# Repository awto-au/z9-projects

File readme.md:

- Note re projhect UUIDs

- IMPORTANT: avoid duplicate schematic UUIDs across shared files

If a shared sheet is copied/renamed (for example in `z9-shared/`), make sure the copied `.kicad_sch` does not keep the same top-level `(uuid "...")` as another active sheet file.

Duplicate UUIDs can cause confusing behavior: sheets may fail to load correctly, references can point to the wrong sheet content, and project/sheet-instance mapping can become unstable.

Safe practice when duplicating a sheet:

- duplicate the file
- open it in KiCad and save-as / resave so a new UUID is generated, or manually replace the top-level UUID with a new one
- re-open the parent project and verify the `Sheetfile` path and `sheet_instances` resolve to the intended file

## Shared Sheet Architecture (as of 2026-04-29)

This repository uses a mixed architecture where core modules are shared across multiple projects via `z9-shared/`, while project-specific functionality remains local.

### Truly Shared Sheets (common UUID across projects)

These sheets have the same top-level UUID and represent unified modules used by multiple projects:

| Sheet Name | UUID | Projects Using | Purpose |
|---|---|---|---|
| shared_usbc.kicad_sch | `1f11bca8-5815-40a7-b8ee-263189e52167` | PDM, console, core | USB Type-C connectivity & power |
| shared_isolated_can.kicad_sch | `01fd732b-d28d-4591-958a-cdee10605b4f` | PDM, console, core | Isolated CAN bus interface |
| shared_ism330dhcx.kicad_sch | `c1bd34f9-1a2e-4e3d-a058-d6dd5157e270` | PDM, console, core | 6-axis IMU / accelerometer |
| shared_buzzer.kicad_sch | `58de86fb-6cef-462e-b9e3-6fa5d0bb0e90` | PDM, console, core | Audio/feedback buzzer |

### Project-Specific or Diverged Sheets

These sheets exist with different UUIDs/content across projects:

| Sheet Name | PDM UUID | Console UUID | Status |
|---|---|---|---|
| stm32.kicad_sch | `6cdc1f96-2079-4699-9b8b-64cd08d3349d` (33K lines) | `4182fd16-8ac6-4c4f-8a6b-17b87a3a1318` (26K lines) | ✅ DE-DUPLICATED — assigned unique UUIDs after significant content divergence |
| connectors.kicad_sch | `62522fec-fb26-4067-a233-5bb78faa120b` | `ff807900-38a7-468c-8c88-36815649564b` | Different modules, project-specific |
| untitled.kicad_sch (power) | `4ea6699b-0436-432c-816e-7adf1044fb41` | `f4d1610f-a9d7-400f-8201-07e24024a234` | Different modules, project-specific |

#### stm32 Divergence Details (resolved 2026-04-29)

PDM and console both previously referenced stm32.kicad_sch with the same UUID (`b85e7fcc-fcb8-4f3f-b9d9-a567574ce4fb`), but the files had diverged significantly:

**PDM stm32 (33K lines, older 2022-04-10 metadata):**
- Comprehensive embedded symbol library (JLCPCB capacitors, resistors)
- ST connector types (STDC14, TagConnect)
- Crystal oscillators (8MHz)
- Specialized connectors (DF40HC3.0-100DS-0.4V51)
- More detailed layout/definitions
- Metadata: "title l8", "company DNT"

**Console stm32 (26K lines, newer 2026 metadata):**
- Simplified schematic focused on MCU core
- Test points instead of dedicated connectors
- Metadata: "company Zero9 - 0-9.au", "Some schematic is shared"

**Resolution:**
- PDM stm32 now UUID: `6cdc1f96-2079-4699-9b8b-64cd08d3349d`
- Console stm32 now UUID: `4182fd16-8ac6-4c4f-8a6b-17b87a3a1318`

These are now independent modules that should not be assumed to be interchangeable. Future maintainers should treat them as separate designs and explicitly sync if unification is desired.

### Console-Only Sheets

- shared_usbc_esp32.kicad_sch (`7f987ba3-810e-4341-b9d4-ad527c98f4c1`) — ESP32 variant of USB-C module

### Core Design Structure (rebuilt 2026-04-29)

Core is now a hierarchical module that references only the truly shared sheets in `z9-shared/`:

```
z9-core.kicad_sch (root)
  ├── z9-shared/shared_usbc.kicad_sch
  ├── z9-shared/shared_isolated_can.kicad_sch
  ├── z9-shared/shared_ism330dhcx.kicad_sch
  └── z9-shared/shared_buzzer.kicad_sch
```

### UUID Deduplication (completed 2026-04-29)

Several shared files had duplicate UUIDs that have since been fixed:

| File | Old UUID | New UUID | Reason |
|---|---|---|---|
| usbc.kicad_sch | `1f11bca8-5815-40a7-b8ee-263189e52167` | `fa8ae3e9-6b30-442f-8590-d93320e7db7b` | Copy of shared_usbc; renamed to prevent collision |
| shared.kicad_sch | `1f11bca8-5815-40a7-b8ee-263189e52167` | `6e9f9a04-b3f3-4667-a147-eb1a8952cf4f` | Duplicate of shared_usbc; fixed |
| shared_5V_LMR54410.kicad_sch | `a7202c14-0f41-48d8-b26c-392947ef0c55` | `c6e889f8-d252-47bb-acac-ee7397c7ab1d` | Duplicate of shared_5V_LMR14206; fixed |

stored in [project name].kicad_pro

snup ####################
  "sheets": [
    [
      "8d063f79-9282-4820-bcf4-1ff3c006cf08",
      "Root"
    ],

then 'root' schmeatic 
snip ############
(kicad_sch
	(version 20250114)
	(generator "eeschema")
	(generator_version "9.0")
	(uuid "8d063f79-9282-4820-bcf4-1ff3c006cf08")
	(paper "A3")
	(title_block
		(date "2024-05-30")
	)

-- project uuids
old pdm 8d063f79-9282-4820-bcf4-1ff3c006cf08
new pdm b643db5c-578e-4b48-aafc-cc4190db582a

shared 

new 0d832c56-2071-4d02-b574-dc412c8c5a75

8d063f79-9282-4820-bcf4-1ff3c006cf08

- KiCad library setup notes

KiCad path management is not the only setting required for these projects.
For the PDM project, the symbol and footprint library tables also need to be configured so ERC can resolve the custom libraries used by the design.

Required custom libraries:

- `dnt_global` = my global symbols
- `dnt` = my global footprints

What was found:

- Project-local footprint table: [z9-pdm/fp-lib-table](/home/dan/git/z9-projects/z9-pdm/fp-lib-table)
- Project-local symbol table: [z9-pdm/sym-lib-table](/home/dan/git/z9-projects/z9-pdm/sym-lib-table)
- Global KiCad footprint table: `/home/dan/.config/kicad/10.0/fp-lib-table`
- Global KiCad symbol table: `/home/dan/.config/kicad/10.0/sym-lib-table`
- The PDM project tables were effectively empty, so KiCad was falling back to global configuration.
- `dnt_global` was configured globally on this machine at `/home/dan/git/dnt.kicad.libs/symbols/dnt_global.kicad_sym`
- `dnt` was configured globally on this machine at `/home/dan/git/dnt.kicad.libs/footprints/dnt.pretty`
- KiCad 10 third-party alternate library content was found under `/home/dan/.local/share/kicad/10.0/3rdparty/`
- That third-party content includes AKL resistor/capacitor/diode libraries, but not exact `PCM_JLCPCB*` library names in the global tables.

Current project-local fix added for PDM:

- `z9-pdm/sym-lib-table` now maps `dnt_global`
- `z9-pdm/sym-lib-table` now maps `PCM_Espressif` to `dnt_global.kicad_sym` because the required ESP32-S3 symbol was already embedded there
- `z9-pdm/fp-lib-table` now maps `dnt`
- `z9-pdm/fp-lib-table` now maps `PCM_Espressif` to `dnt.kicad.libs/footprints/PCM_Espressif.pretty`
- `z9-pdm/sym-lib-table` also maps `PCM_JLCPCB-Resistors`, `PCM_JLCPCB-Capacitors`, and `PCM_JLCPCB-Diodes` to get ERC closer to usable
- `z9-pdm/fp-lib-table` also maps `PCM_JLCPCB`
- The required Espressif footprint files `ESP32-S3-WROOM-1.kicad_mod` and `ESP32-S3-WROOM-1U.kicad_mod` were copied from `https://github.com/espressif/kicad-libraries` into `dnt.kicad.libs/footprints/PCM_Espressif.pretty`
- The matching Espressif STEP models were copied into `dnt.kicad.libs/models/`

Result:

- ERC on PDM dropped from `1 error, 675 warnings` to `1 error, 229 warnings`
- Most of the missing-library noise was removed
- `PCM_Espressif` now resolves from repo-local library content instead of requiring a separate KiCad add-on install on this machine
- Remaining warnings show that some `PCM_JLCPCB*` symbols and footprints still do not exist under the currently available local libraries, so installing or restoring the original PCM/JLC libraries is still needed for a clean ERC result

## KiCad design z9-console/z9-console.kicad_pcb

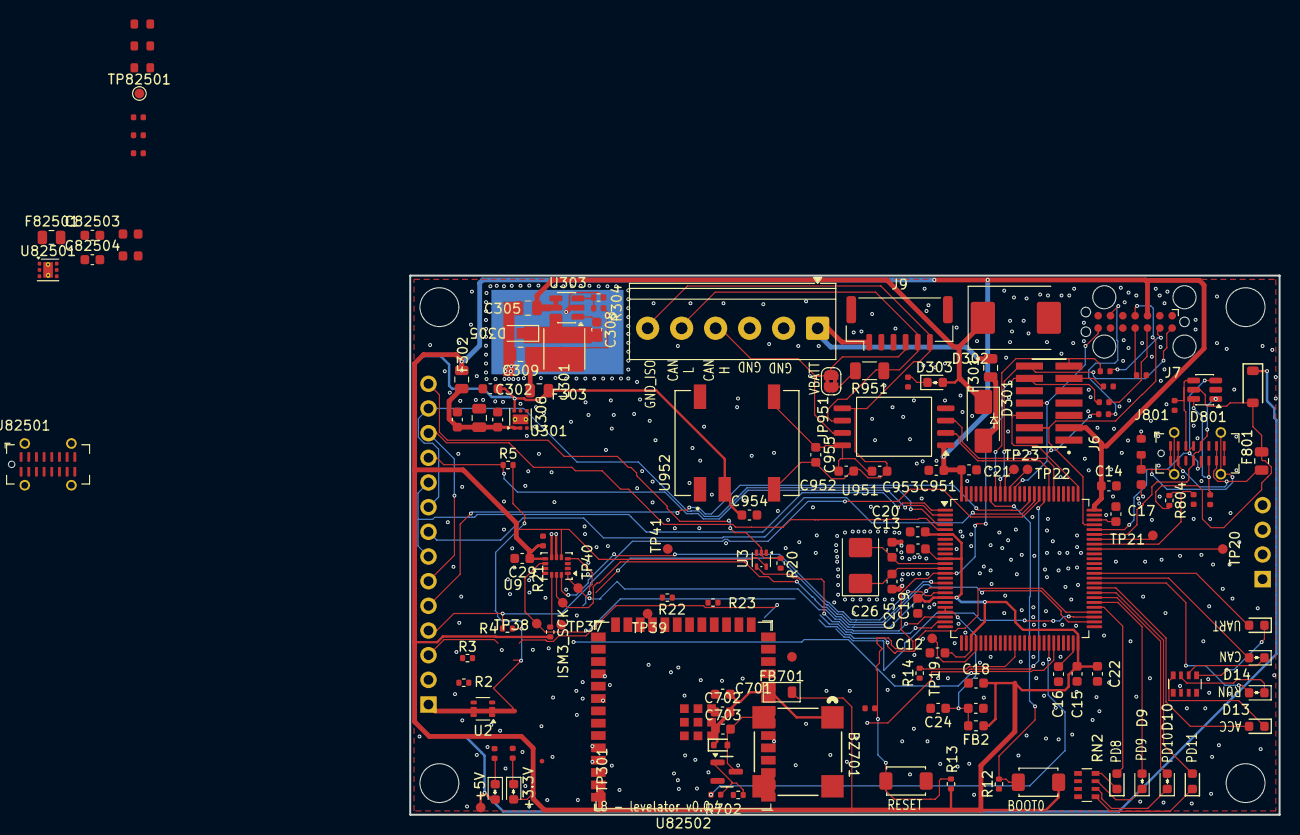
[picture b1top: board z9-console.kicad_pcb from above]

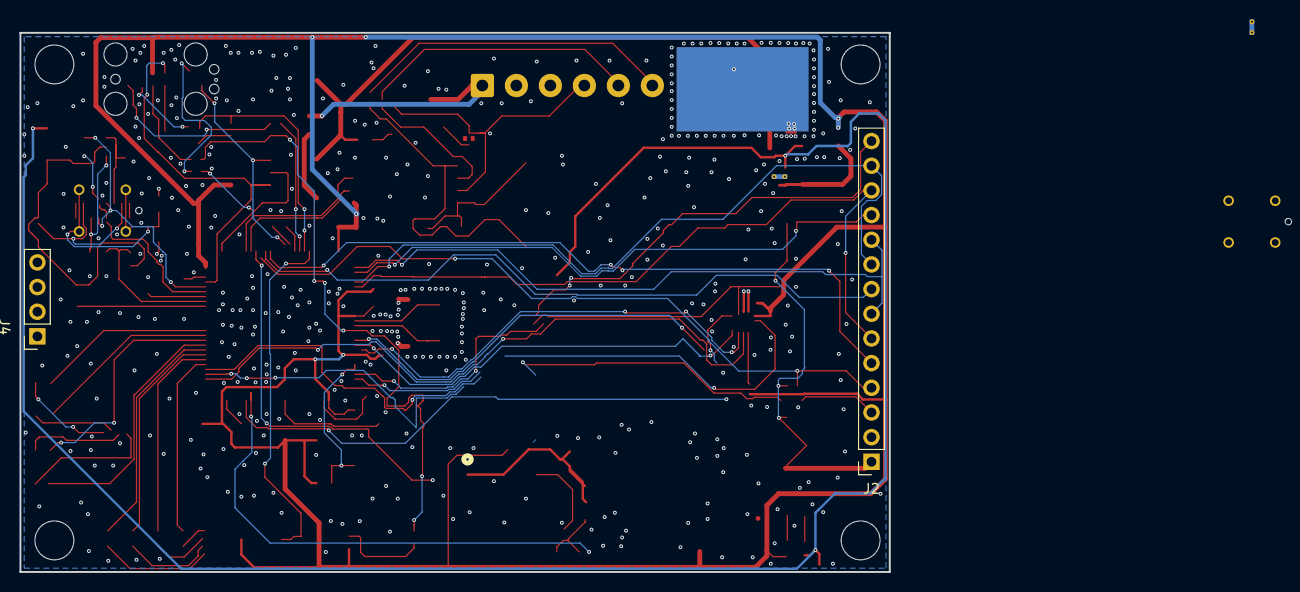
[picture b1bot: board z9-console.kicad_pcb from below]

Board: 2 copper layers, 89.5 x 55.5 mm, 143 parts (2 on the bottom side), 100 nets.

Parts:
BZ701: Buzzer_-_MLT-8530; Buzzer - MLT-8530_JHE
C11: 10nF; C_0402
C12, C13, C14, C15, C18, C19, C20, C21, C24, C306, C308, C702, C703, C951, C953, C82503: 100nF; C_0603_1608Metric
C16, C17: 2.2uF; C_0603_1608Metric
C22, C29, C302, C701, C952, C954, C955, C82504: 10uF; C_0603_1608Metric
C23, C303: 1uF; C_0603_1608Metric
C25, C26: 18pF; C_0603_1608Metric
C28: 100nF; C_0402
C304, C309: 22uF; C_0805_2012Metric
C305: 10uF; C_0805_2012Metric
C801: 47nF; C_0603
C82501, C82502: 10uF; C_0603
D8, D11, D12, D15: LED-YELLOW; D_0603
D9, D13: LED-WHITE; LED_0603_1608Metric - polarity
D10, D14, D303, D304, D306: LED-RED; LED_0603_1608Metric - polarity
D301: SS54; D_SMA - polarity
D302: SM15T100CA; D_SMC
D305: V1P6-M3/H 60V 1A; D_MicroSMP_AK
D701: RB751S-40; D_SOD-523
D801: SRV05-4; SOT-23-6
D802: B5819W SL; D_SOD-123
F301, F302, F303, F801: Fuse; Fuse_0805_2012Metric
F82501: Fuse_16V_500mA_100A_1A_150mΩ_0805_PTC; Fuse_0805_2012Metric
FB2: 4.7uH; L_0603_1608Metric
FB701: F_0805_2012Metric
H901, H902, H903, H904: MountingHole; MountingHole_4mm
J2: LCD 3.2" 240x320 Conn_01x14_Pin; PinSocket_1x14_P2.54mm_Vertical
J4: Conn_01x04_Pin; PinSocket_1x04_P2.54mm_Vertical
J6: ST_STDC14 - SAMTEC_FTSH-107-01-F-DV-K-Fix; Conn_SAMTEC_FTSH-107-01-F-DV-K-Fix
J7: TC2070 - TAG Connect; Tag-Connect_TC2070-IDC-FP_2x07_P1.27mm_Vertical
J9: JST GH; JST_GH_BM06B-GHS-TBT_1x06-1MP_P1.25mm_Vertical
J10: Screw_Terminal_01x06; TerminalBlock_Phoenix_PT-1,5-6-3.5-H_1x06_P3.50mm_Horizontal
J801, J82501: USB_C_Receptacle_USB2.0_16P; USB_C_Receptacle_G-Switch_GT-USB-7051x
JP951: SolderJumper_2_Bridged; SolderJumper-2_P1.3mm_Bridged2Bar_RoundedPad1.0x1.5mm
L301: 3.3uH; L_Sunlord_SWPA4030S
Q701: AO3400A; Q_SOT-23
R2, R3, R4, R5, R12, R13, R14, R20, R21, R22, R23, R304, R702, R804: 10K; R_0402_1005Metric
R15, R16, R17, R18, R19, R701: 100R; R_0402
R301, R302, R305: 2.2K; R_0402
R303: 56K; R_0402
R801: 1MΩ; R_0603
R802, R803, R82504, R82505, R82506: 5.1kΩ; R_0402
R805: 2.2k; R_0402
R951: 120R; R_1206_3216Metric
R82501, R82502: 100kΩ; R_0603
R82503: 47Ω; R_0603
RN2, RN3: 1k; R_Array_Convex_4x0603
SW2, SW3: SW_Push; SW_TS-1088-AR02016
TP18: PA1; TestPoint_Pad_D1.0mm FP .6R
TP19: PA4; TestPoint_Pad_D1.0mm FP .6R
TP20: PA8; TestPoint_Pad_D1.0mm FP .6R
TP21: PA10; TestPoint_Pad_D1.0mm FP .6R
TP22: PB4; TestPoint_Pad_D1.0mm FP .6R
TP23: PB5; TestPoint_Pad_D1.0mm FP .6R
TP37: ISM_CS; TestPoint_Pad_D1.0mm FP .6R
TP38: ISM_INT1; TestPoint_Pad_D1.0mm FP .6R
TP39: ISM_INT2; TestPoint_Pad_D1.0mm FP .6R
TP40: ISM_SDO; TestPoint_Pad_D1.0mm FP .6R
TP41: ISM_SDI; TestPoint_Pad_D1.0mm FP .6R
TP42: ISM3_SCK; TestPoint_Pad_D1.0mm FP .6R
TP301: +3.3V; TestPoint_Pad_D1.0mm FP .6R
TP302: 5V; TestPoint_Pad_D1.0mm FP .6R
TP82501: PE0; TestPoint_Pad_D1.0mm
U2: TPS22919DCKR; SOT-363_SC-70-6
U3: SN74LVC1G14DRLR; SOT-553
U8: STM32F427V_G-I_Tx; LQFP-100_14x14mm_P0.5mm
U9: ISM330DHCX; LGA-14_3x2.5mm_P0.5mm_LayoutBorder3x4y
U301, U82501: TLV76733DRVx; WSON-6-1EP_2x2mm_P0.65mm_EP1x1.6mm_ThermalVias
U303: LMR14006YDDCR; SOT-23-6
U951: ISO1042-Q1; SOIC-8_7.5x5.85mm_P1.27mm
U952: B0505XT-1WR3; B0505_Isolated_SMD
U82502: ESP32-S3-WROOM-1; ESP32-S3-WROOM-1U
X2: 8MHz 20pF; Crystal_SMD_5032-2Pin_5.0x3.2mm

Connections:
+3.3V: C12.2, C13.2, C14.2, C15.2, C18.2, C19.2, C20.2, C21.2, C22.2, C28.1, C29.1, C951.1, D304.2 (A), F302.2, FB2.1, FB701.2, J6.3 (VCC), J7.3 (VCC), R13.1, R21.2, SW2.2 (B), TP301.1, U2.1 (VIN), U3.5 (VCC), U8.6 (VBAT), U8.11 (VDD), U8.19 (VDD), U8.28 (VDD), U8.50 (VDD), U8.75 (VDD), U8.100 (VDD), U9.5 (VDDIO), U9.8 (VDD), U951.1 (VCC1)
+5V: C302.1, C954.1, C82501.1, D306.2 (A), D802.1, F303.2, TP302.1, U301.6 (IN), U952.2 (+VIN), U82501.6 (IN)
/+5V_ISO: C952.1, C953.1, C955.1, U951.8 (VCC2), U952.5 (+VOUT)
/CAN1_RX: U8.81 (PD0), U951.3 (RXD)
/CAN1_TX: U8.82 (PD1), U951.2 (TXD)
/CAN_H: J9.4, J10.4, JP951.2 (B), U951.7 (CANH)
/CAN_L: J9.5, J10.5, R951.1, U951.6 (CANL)
/GND_ISO: C952.2, C953.2, C955.2, J9.6, J10.6, U951.5 (GND2), U952.4 (-VOUT)
/LCD_DC: J2.5 (D/C), U8.86 (PD5)
/LCD_LED: J2.8 (LED), U8.85 (PD4)
/LCD_ON: R2.2, U2.3 (ON), U8.45 (PE14)
/LCD_RESET: J2.4 (RESET), R4.1, U8.84 (PD3)
/MCU/BOOT0: R12.2, SW2.1 (A), U8.94 (BOOT0)
/MCU/BOOT1: R14.2, U8.37 (PB2)
/MCU/NRST: C11.2, J6.12 (~RST), R13.2, R17.1, SW3.2 (B), U8.14 (NRST)
/MCU/PA1: TP18.1, U8.24 (PA1)
/MCU/PA4: TP19.1, U8.29 (PA4)
/MCU/PA8: TP20.1, U8.67 (PA8)
/MCU/PB4: TP22.1, U8.90 (PB4)
/MCU/PB5: TP23.1, U8.91 (PB5)
/MCU/PD8: D8.2, U8.55 (PD8)
/MCU/PD9: D9.2 (A), U8.56 (PD9)
/MCU/PD10: D10.2 (A), U8.57 (PD10)
/MCU/PD11: D11.2, U8.58 (PD11)
/MCU/PD12: D12.2, U8.59 (PD12)
/MCU/PD13: D13.2 (A), U8.60 (PD13)
/MCU/PD14: D14.2 (A), U8.61 (PD14)
/MCU/PD15: D15.2, U8.62 (PD15)
/MCU/RCC_OSC_IN: C25.1, U8.12 (PH0), X2.2
/MCU/RCC_OSC_OUT: C26.1, U8.13 (PH1), X2.1
/MCU/SYS_JTCK-SWCLK: J6.6 (JCLK/SWCLK), R18.1, U8.76 (PA14)
/MCU/SYS_JTDO-SWO: J6.8 (JTDO/SWO), J7.8 (JTDO/SWO), U8.89 (PB3)
/MCU/SYS_JTMS-SWDIO: J6.4 (JTMS/SWDIO), J7.4 (JTMS/SWDIO), U8.72 (PA13)
/MCU/USART1_RX: J6.13 (VCP_RX), R19.1, U8.93 (PB7)
/MCU/USART1_TX: J6.14 (VCP_TX), J7.14 (VCP_TX), U8.92 (PB6)
/PE13: R701.2, U8.44 (TIM1_CH3)
/SPI2_CS: R21.1, TP37.1, U8.16 (PC1), U9.12 (CS)
/SPI2_IRQ: R22.2, TP39.1, U8.53 (PB14), U9.4 (INT1)
/SPI2_IRQ2: R23.2, TP38.1, U8.54 (PB15), U9.9 (INT2)
/SPI2_SCK: TP42.1, U8.52 (PB13), U9.13 (SCL)
/SPI2_SDI: TP40.1, U8.17 (PC2), U9.1 (SDO/SA0)
/SPI2_SDO: TP41.1, U8.18 (PC3), U9.14 (SDA)
/SPI4_CS_1: J2.11 (T_CS), R5.1, U8.2 (PE3)
/SPI4_CS_2: J2.3 (CS), R3.1, U8.83 (PD2)
/SPI4_SCK: J2.7 (SCK), J2.10 (T_SCK), U8.1 (PE2)
/SPI4_SDI: J2.9 (SDO), J2.13 (T_SDO), U8.4 (PE5)
/SPI4_SDO: J2.6 (SDI), J2.12 (T_SDI), U8.5 (PE6)
/SYS_WAKEUP: U3.4, U8.23 (PA0)
/USB_OTG_FS_DM: D801.1, J801.A7 (D-), J801.B7 (D-), U8.70 (PA11)
/USB_OTG_FS_DP: D801.3, J801.A6 (D+), J801.B6 (D+), U8.71 (PA12)
/USB_OTG_FS_VBUS: R804.1, R805.2, U8.68 (PA9)
/VBATT: F301.1, J9.1, J10.1
/shared_esp32/ESP_EN: R82501.1, U82502.3 (EN)
GND: C11.1, C12.1, C13.1, C14.1, C15.1, C16.2, C17.2, C18.1, C19.1, C20.1, C21.1, C22.1, C23.1, C24.2, C25.2, C26.2, C28.2, C29.2, C302.2, C303.1, C304.2, C305.2, C306.2, C309.2, C701.2, C702.1, C801.2, C951.2, C954.2, C82501.2, C82502.2, C82503.2, C82504.2, D302.2 (A2), D305.2 (A), D801.2, J2.2 (GND), J6.5 (GND), J6.7 (GND), J7.5 (GND), J7.7 (GND), J9.2, J9.3, J10.2, J10.3, J801.A1 (GND), J801.A12 (GND), J801.B1 (GND), J801.B12 (GND), J82501.A1 (GND), J82501.A12 (GND), J82501.B1 (GND), J82501.B12 (GND), J82501.S1 (SHIELD), Q701.2 (S), R2.1, R12.1, R14.1, R15.2, R16.2, R20.1, R22.1, R23.1, R301.1, R302.1, R304.1, R305.1, R702.1, R801.2, R802.1, R803.1, R805.1, R82501.2, R82505.1, R82506.1, RN2.5 (R4.2), RN2.6 (R3.2), RN2.7 (R2.2), RN2.8 (R1.2), RN3.5 (R4.2), RN3.6 (R3.2), RN3.7 (R2.2), RN3.8 (R1.2), SW3.1 (A), U2.2 (GND), U3.3 (GND), U8.10 (VSS), U8.20 (VSSA), U8.27 (VSS), U8.74 (VSS), U8.99 (VSS), U9.6 (GND), U9.7 (GND), U301.3 (GND), U301.5 (GND), U301.7 (PAD), U303.2 (GND), U951.4 (GND1), U952.1 (-VIN), U82501.3 (GND), U82501.5 (GND), U82501.7 (PAD), U82502.1 (GND), U82502.40 (GND), U82502.41 (GND)
unnamed: BZ701.1 (+), C701.1, C702.2, C703.1, D701.1, FB701.1
unnamed: BZ701.2 (-), C703.2, D701.2, Q701.3 (D)
unnamed: C309.1, F303.1, L301.2, R303.1
unnamed: D9.1 (K), RN2.3 (R3.1)
unnamed: D10.1 (K), RN2.2 (R2.1)
unnamed: D13.1 (K), RN3.3 (R3.1)
unnamed: D14.1 (K), RN3.2 (R2.1)
unnamed: D301.2 (A), F301.2
unnamed: C305.1, D301.1 (K), D302.1 (A1), D303.2 (A), U303.4 (~SHDN), U303.5 (VIN)
unnamed: D303.1 (K), R301.2
unnamed: D304.1 (K), R302.2
unnamed: C308.2, D305.1 (K), L301.1, U303.6 (SW)
unnamed: D306.1 (K), R305.2
unnamed: D801.5, D802.2, F801.2, R804.2
unnamed: F801.1, J801.A4 (VBUS), J801.A9 (VBUS), J801.B4 (VBUS), J801.B9 (VBUS)
unnamed: J2.14 (T_IRQ), R20.2, U3.2
unnamed: J2.1 (VCC), R3.2, R4.2, R5.2, U2.5 (QOD), U2.6 (VOUT)
unnamed: J6.11 (GNDDetect), R15.1
unnamed: J7.11 (GNDDetect), R16.1
unnamed: J7.6 (JCLK/SWCLK), R18.2
unnamed: J7.13 (VCP_RX), R19.2
unnamed: J7.12 (~RST), R17.2
unnamed: D801.4, J801.A5 (CC1), R803.2
unnamed: D801.6, J801.B5 (CC2), R802.2
unnamed: C801.1, J801.S1 (SHIELD), R801.1
unnamed: J82501.A5 (CC1), R82506.2
unnamed: J82501.B5 (CC2), R82505.2
unnamed: JP951.1 (A), R951.2
unnamed: Q701.1 (G), R701.1, R702.2
unnamed: D11.1, RN2.1 (R1.1)
unnamed: D8.1, RN2.4 (R4.1)
unnamed: D15.1, RN3.1 (R1.1)
unnamed: D12.1, RN3.4 (R4.1)
unnamed: TP21.1, U8.69 (PA10)
unnamed: C16.1, U8.49 (VCAP_1)
unnamed: C17.1, U8.73 (VCAP_2)
unnamed: C23.2, C24.1, FB2.2, U8.21 (VREF+), U8.22 (VDDA)
unnamed: C303.2, C304.1, C306.1, F302.1, U301.1 (OUT), U301.2 (SNS)
unnamed: C308.1, U303.1 (CB)
unnamed: R303.2, R304.2, U303.3 (FB)
unnamed: C82502.1, F82501.1, U82501.1 (OUT), U82501.2 (SNS)
unnamed: C82503.1, C82504.1, F82501.2, R82502.1, TP82501.1, U82502.2 (3V3)
unnamed: R82502.2, R82504.1, U82502.27 (GPIO0/BOOT)
unnamed: J82501.A7 (D-), J82501.B7 (D-), U82502.13 (GPIO19/U1RTS/ADC2_CH8/CLK_OUT2/USB_D-)
unnamed: J82501.A6 (D+), J82501.B6 (D+), U82502.14 (GPIO20/U1CTS/ADC2_CH9/CLK_OUT1/USB_D+)
unnamed: R82503.1, U82502.37 (U0TXD/GPIO43/CLK_OUT1)

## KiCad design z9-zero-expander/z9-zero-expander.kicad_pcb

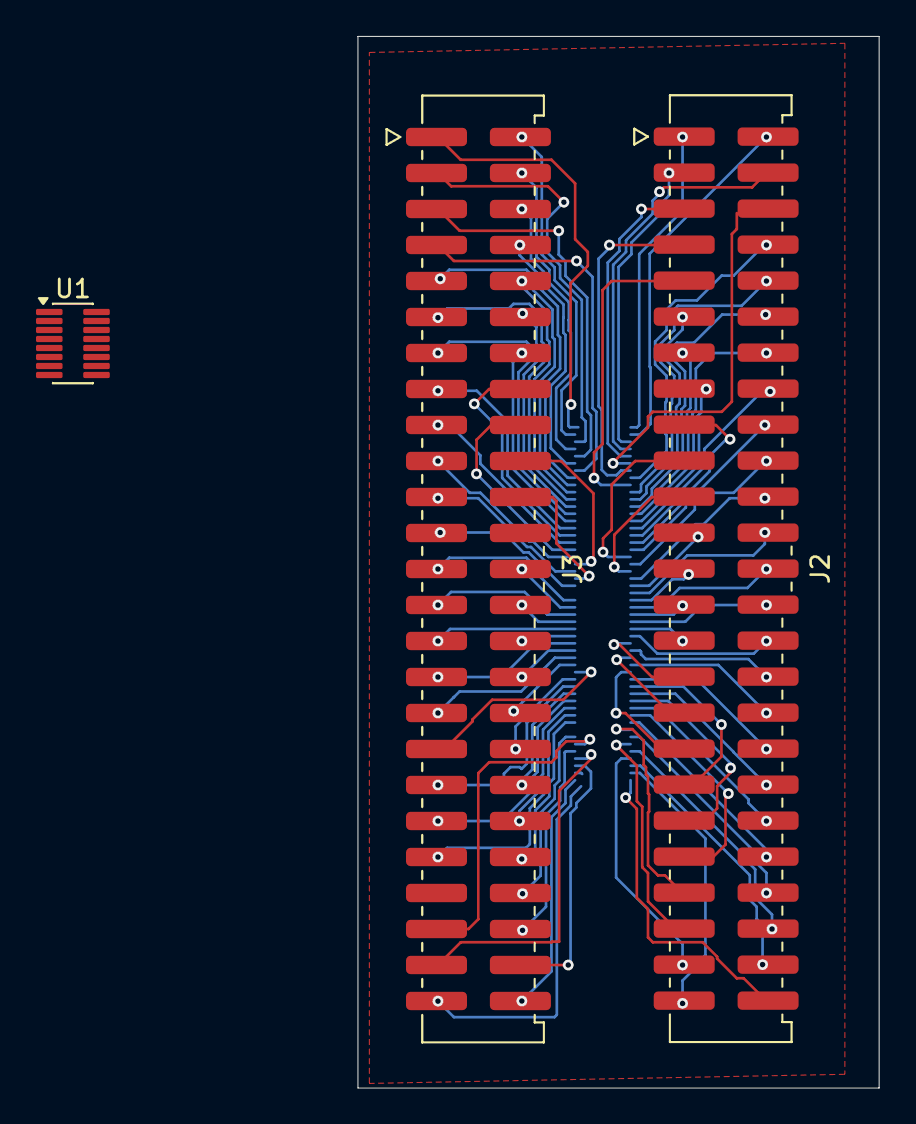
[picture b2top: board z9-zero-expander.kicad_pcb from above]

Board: 2 copper layers, 29.0 x 58.4 mm, 4 parts (1 on the bottom side), 100 nets.

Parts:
J1: Conn_DF40HC3.0-100DP-0.4V51; Hirose_DF40C-100DP-0.4V_2x50-1MP_P0.4mm
J2, J3: Conn_01x50; Samtec_LTMM-125-02-X-D-SM_2x25_P2.0mm_Header_Vertical
U1: TMUX1574DYY; Texas_DYY0016A_TSOT-23-16_2x4.2mm_P0.5mm

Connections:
unnamed: J1.51, J2.1
unnamed: J1.52, J2.2
unnamed: J1.53, J2.3
unnamed: J1.54, J2.4
unnamed: J1.55, J2.5
unnamed: J1.56, J2.6
unnamed: J1.57, J2.7
unnamed: J1.58, J2.8
unnamed: J1.59, J2.9
unnamed: J1.60, J2.10
unnamed: J1.61, J2.11
unnamed: J1.62, J2.12
unnamed: J1.63, J2.13
unnamed: J1.64, J2.14
unnamed: J1.65, J2.15
unnamed: J1.66, J2.16
unnamed: J1.67, J2.17
unnamed: J1.68, J2.18
unnamed: J1.69, J2.19
unnamed: J1.70, J2.20
unnamed: J1.71, J2.21
unnamed: J1.72, J2.22
unnamed: J1.73, J2.23
unnamed: J1.74, J2.24
unnamed: J1.75, J2.25
unnamed: J1.76, J2.26
unnamed: J1.77, J2.27
unnamed: J1.78, J2.28
unnamed: J1.79, J2.29
unnamed: J1.80, J2.30
unnamed: J1.81, J2.31
unnamed: J1.82, J2.32
unnamed: J1.83, J2.33
unnamed: J1.84, J2.34
unnamed: J1.85, J2.35
unnamed: J1.86, J2.36
unnamed: J1.87, J2.37
unnamed: J1.88, J2.38
unnamed: J1.89, J2.39
unnamed: J1.90, J2.40
unnamed: J1.91, J2.41
unnamed: J1.92, J2.42
unnamed: J1.93, J2.43
unnamed: J1.94, J2.44
unnamed: J1.95, J2.45
unnamed: J1.96, J2.46
unnamed: J1.97, J2.47
unnamed: J1.98, J2.48
unnamed: J1.99, J2.49
unnamed: J1.100, J2.50
unnamed: J1.1, J3.1
unnamed: J1.2, J3.2
unnamed: J1.3, J3.3
unnamed: J1.4, J3.4
unnamed: J1.5, J3.5
unnamed: J1.6, J3.6
unnamed: J1.7, J3.7
unnamed: J1.8, J3.8
unnamed: J1.9, J3.9
unnamed: J1.10, J3.10
unnamed: J1.11, J3.11
unnamed: J1.12, J3.12
unnamed: J1.13, J3.13
unnamed: J1.14, J3.14
unnamed: J1.15, J3.15
unnamed: J1.16, J3.16
unnamed: J1.17, J3.17
unnamed: J1.18, J3.18
unnamed: J1.19, J3.19
unnamed: J1.20, J3.20
unnamed: J1.21, J3.21
unnamed: J1.22, J3.22
unnamed: J1.23, J3.23
unnamed: J1.24, J3.24
unnamed: J1.25, J3.25
unnamed: J1.26, J3.26
unnamed: J1.27, J3.27
unnamed: J1.28, J3.28
unnamed: J1.29, J3.29
unnamed: J1.30, J3.30
unnamed: J1.31, J3.31
unnamed: J1.32, J3.32
unnamed: J1.33, J3.33
unnamed: J1.34, J3.34
unnamed: J1.35, J3.35
unnamed: J1.36, J3.36
unnamed: J1.37, J3.37
unnamed: J1.38, J3.38
unnamed: J1.39, J3.39
unnamed: J1.40, J3.40
unnamed: J1.41, J3.41
unnamed: J1.42, J3.42
unnamed: J1.43, J3.43
unnamed: J1.44, J3.44
unnamed: J1.45, J3.45
unnamed: J1.46, J3.46
unnamed: J1.47, J3.47
unnamed: J1.48, J3.48
unnamed: J1.49, J3.49
unnamed: J1.50, J3.50

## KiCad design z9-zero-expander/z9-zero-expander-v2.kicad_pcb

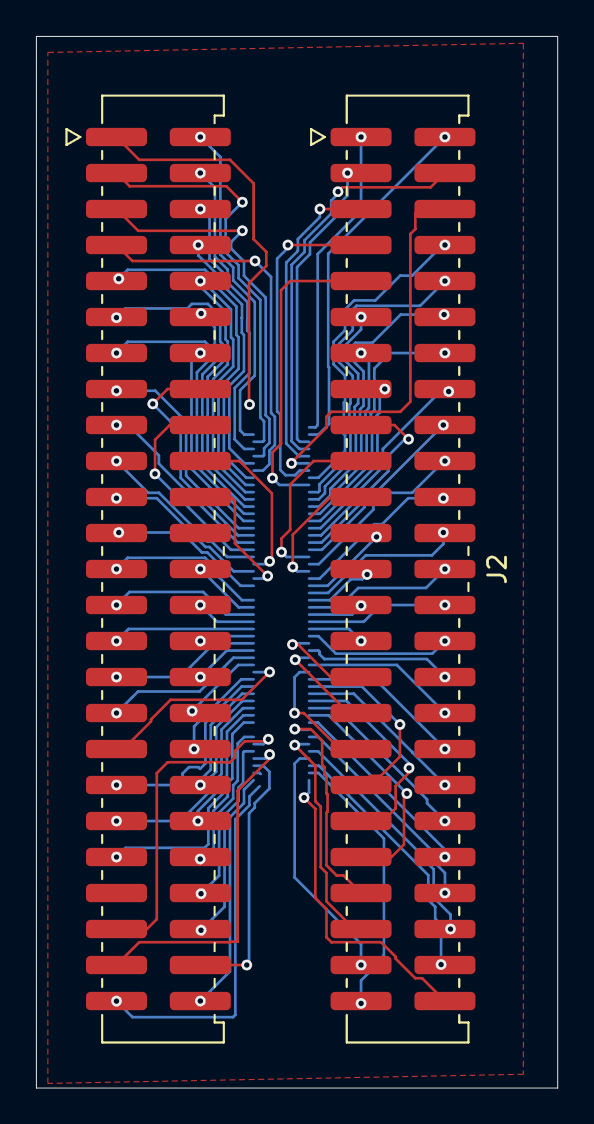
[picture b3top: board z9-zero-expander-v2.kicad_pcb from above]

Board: 2 copper layers, 29.0 x 58.4 mm, 3 parts (1 on the bottom side), 100 nets.

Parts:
J1: Conn_DF40HC3.0-100DP-0.4V51; Hirose_DF40C-100DP-0.4V_2x50-1MP_P0.4mm
J2, J3: Conn_01x50; Samtec_LTMM-125-02-X-D-SM_2x25_P2.0mm_Header_Vertical

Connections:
unnamed: J1.1, J2.1
unnamed: J1.2, J2.2
unnamed: J1.3, J2.3
unnamed: J1.4, J2.4
unnamed: J1.5, J2.5
unnamed: J1.6, J2.6
unnamed: J1.7, J2.7
unnamed: J1.8, J2.8
unnamed: J1.9, J2.9
unnamed: J1.10, J2.10
unnamed: J1.11, J2.11
unnamed: J1.12, J2.12
unnamed: J1.13, J2.13
unnamed: J1.14, J2.14
unnamed: J1.15, J2.15
unnamed: J1.16, J2.16
unnamed: J1.17, J2.17
unnamed: J1.18, J2.18
unnamed: J1.19, J2.19
unnamed: J1.20, J2.20
unnamed: J1.21, J2.21
unnamed: J1.22, J2.22
unnamed: J1.23, J2.23
unnamed: J1.24, J2.24
unnamed: J1.25, J2.25
unnamed: J1.26, J2.26
unnamed: J1.27, J2.27
unnamed: J1.28, J2.28
unnamed: J1.29, J2.29
unnamed: J1.30, J2.30
unnamed: J1.31, J2.31
unnamed: J1.32, J2.32
unnamed: J1.33, J2.33
unnamed: J1.34, J2.34
unnamed: J1.35, J2.35
unnamed: J1.36, J2.36
unnamed: J1.37, J2.37
unnamed: J1.38, J2.38
unnamed: J1.39, J2.39
unnamed: J1.40, J2.40
unnamed: J1.41, J2.41
unnamed: J1.42, J2.42
unnamed: J1.43, J2.43
unnamed: J1.44, J2.44
unnamed: J1.45, J2.45
unnamed: J1.46, J2.46
unnamed: J1.47, J2.47
unnamed: J1.48, J2.48
unnamed: J1.49, J2.49
unnamed: J1.50, J2.50
unnamed: J1.51, J3.1
unnamed: J1.52, J3.2
unnamed: J1.53, J3.3
unnamed: J1.54, J3.4
unnamed: J1.55, J3.5
unnamed: J1.56, J3.6
unnamed: J1.57, J3.7
unnamed: J1.58, J3.8
unnamed: J1.59, J3.9
unnamed: J1.60, J3.10
unnamed: J1.61, J3.11
unnamed: J1.62, J3.12
unnamed: J1.63, J3.13
unnamed: J1.64, J3.14
unnamed: J1.65, J3.15
unnamed: J1.66, J3.16
unnamed: J1.67, J3.17
unnamed: J1.68, J3.18
unnamed: J1.69, J3.19
unnamed: J1.70, J3.20
unnamed: J1.71, J3.21
unnamed: J1.72, J3.22
unnamed: J1.73, J3.23
unnamed: J1.74, J3.24
unnamed: J1.75, J3.25
unnamed: J1.76, J3.26
unnamed: J1.77, J3.27
unnamed: J1.78, J3.28
unnamed: J1.79, J3.29
unnamed: J1.80, J3.30
unnamed: J1.81, J3.31
unnamed: J1.82, J3.32
unnamed: J1.83, J3.33
unnamed: J1.84, J3.34
unnamed: J1.85, J3.35
unnamed: J1.86, J3.36
unnamed: J1.87, J3.37
unnamed: J1.88, J3.38
unnamed: J1.89, J3.39
unnamed: J1.90, J3.40
unnamed: J1.91, J3.41
unnamed: J1.92, J3.42
unnamed: J1.93, J3.43
unnamed: J1.94, J3.44
unnamed: J1.95, J3.45
unnamed: J1.96, J3.46
unnamed: J1.97, J3.47
unnamed: J1.98, J3.48
unnamed: J1.99, J3.49
unnamed: J1.100, J3.50

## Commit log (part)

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2025-11-13 add new PDF documentation files for various components
2025-11-13 update .gitignore to include additional autosave files for z9-pdm
2025-11-13 remove outdated backup zip files from z9-console directory
2025-11-13 Add DTP13-4P documentation and files
    - Added DTP13-4P.zip containing relevant resources.
    - Included License.txt outlining usage terms and conditions for the models.
    - Created TE_DTP13-4P.kicad_mod for KiCad PCB design integration.
    - Added how-to-import.htm for redirecting users to the import guide on SnapEDA.
2025-11-13 Add new shapes to sensor schematic for improved design clarity
2025-11-13 Implement feature X to enhance user experience and fix bug Y in module Z
2025-11-13 Update column widths and sorting options in net inspector panel for improved usability
2025-11-13 Update references and column widths in schematic and project files
    - Adjusted column widths in z9-pdm.kicad_prl for better layout.
    - Updated component references in shared_isolated_can.kicad_sch to specific identifiers (e.g., C? to C953, R? to R951).
    - Modified references in shared_usbc.kicad_sch to include specific component identifiers (e.g., D? to D801, R? to R805).
    - Ensured all power references are updated to their specific identifiers (e.g., #PWR? to #PWR0107).
2025-11-13 removed dil24
2025-11-13 Remove unused graphical elements from sensor schematic for cleaner design
2025-11-13 Remove unused SPI labels and text from schematic for cleaner design
2025-11-13 Remove unused labels and wires from schematic SD Card junk
2025-11-14 Add shared_ism330dhcx schematic and update project configuration - Buzzer chaNGES 3.3v BEADS ANDCAPS - Created a new schematic file for the shared_ism330dhcx component. - Updated the z9-shared projec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
2025-11-14 fix footprint
2025-11-14 Adjust fuse properties and reposition value label for clarity
2025-11-14 Update net inspector panel column width for improved visibility
2025-11-14 Remove unused ST_SENSOR text from schematic
2025-11-16 Update schematic and project settings for shared components
    - Changed the starting annotation number from 700 to 975 in the project configuration.
    - Added a new shared schematic sheet named "shared_isolated_can_ps" with relevant properties and instances.
    - Included a cautionary text in the schematic to avoid moving components and reannotating to prevent loss of links.
2025-11-16 Add no-connect pins and ISO power pins to the schematic for shared components
2025-11-16 Add PWR_FLAG symbols to schematic for power source indication
2025-11-16 Add initial schematic file for shared isolated CAN power supply
2025-11-16 Update schematic and project configuration
    - Changed the starting number for annotation in the project configuration from 300 to 700.
    - Removed the "+5V_ISO" label from the schematic.
    - Adjusted the position of the "PE13" label.
    - Added a new "VBATT" label in the schematic.
    - Updated the "shared buzzer" sheet reference, changing its UUID and properties.
    - Modified the pin configuration for the "BUZZER" input in the schematic.
2025-11-16 Remove outdated backup zip file from shared backups
2025-11-16 Adjust USB label positions and sheet properties for improved layout
2025-11-16 Remove unused components and adjust annotation start number in project files
2025-11-16 Remove obsolete schematic files for shared isolated CAN power supply
2025-11-16 Update reference designators and adjust USB label positions for consistency
2025-11-16 Update error handling for footprint and junction issues in project settings
2025-11-17 Add z9-console project references and update component properties in shared_buzzer schematic
2025-11-17 Update KiCad project files and schematic references
    - Changed active layer in z9-console.kicad_prl from 5 to 0.
    - Removed a missing courtyard warning from z9-console.kicad_pro.
    - Updated library footprint mismatch handling from ignore to error in z9-console.kicad_pro.
    - Changed net conflict handling from warning to error in z9-console.kicad_pro.
    - Updated silk over copper and silk overlap handling from warning to ignore in z9-console.kicad_pro.
    - Changed via dangling handling from warning to error in z9-console.kicad_pro.
2025-11-17 mainly route vip
2025-11-17 route plugds
2025-11-17 Rename labels in schematic for consistency and clarity
2025-11-17 rearrange power section for inductive load and fix fusing (none) wire uyp second vipower
2025-11-19 connector routing
2025-11-19 Update board settings: reset hidden nets, adjust high contrast mode, and refine selection filter options
2025-11-20 vipower fixes etc
2025-11-22 Update active layer and visible layers in z9-pdm.kicad_prl; remove autosave lock file
2025-12-01 Update active layer and visible layers in KiCad project files
    - Changed the active layer from 6 to 0 in z9-pdm.kicad_prl to reset the default layer.
    - Modified the visible layers string in z9-pdm.kicad_prl for better layer visibility management.
    - Cleared the DRC exclusions in z9-pdm.kicad_pro to remove unnecessary footprint symbol mismatch entries.
2025-12-01 Refactor junctions and wires in connectors schematic; remove unused labels and pins in z9-pdm schematic; update project settings to ignore four-way junction warnings; enhance ERC settings in shared p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
2025-12-01 Update DNP property for J4 connector and correct footprint reference in STM32 schematic
2025-12-01 Add PWR_FLAG symbol to indicate power source in schematic; update junctions and wires accordingly
2025-12-01 Remove unused wire from connectors schematic to clean up the design
2025-12-02 Refactor diode properties in power schematic; remove unused silkscreen, package, and vendor fields for clarity
2025-12-04 Update visible_layers in z9-pdm.kicad_prl to adjust layer visibility settings
2025-12-10 fix netclasses and vias
2026-01-05 pre replicate analogue chans
2026-01-06 laypout ad section canl/h swap
2026-01-06 routing
2026-01-06 pre cleanups
2026-01-09 keep on xconnectors
2026-01-11 clean sch
2026-01-14 drc etc
2026-02-06 pre kc update
2026-02-06 pre kicad update
2026-02-24 new fuse and ideal diode
2026-02-26 post 5v lay references lost
2026-03-02 pre final pdm erc
2026-03-05 passes sch drc
2026-03-05 pcb drc ok
2026-03-10 submitted to jlcpcb
2026-03-17 fixced missing vias
2026-03-17 approved by jlc
2026-03-26 moved to kicad v10 and commit expander
2026-04-29 z9-zero-expander: migrate to KiCad 10 and add new sub-sheets
2026-04-29 kicad: migrate z9-pdm, z9-console and z9-shared projects to KiCad 10
2026-04-29 z9-pdm: rename 12V net label and add wire connections
2026-04-29 z9-zero-expander: update subproject commit reference
2026-04-29 z9-pdm: move board image into images directory
2026-04-29 gitignore: ignore local .history directories
2026-04-29 update KiCad library configurations for PDM project to resolve ERC issues
2026-04-29 Core add KiCad library and schematic updates, including new components and ERC report
2026-04-29 update l8-harness.kicad_prl to add prototype zone fills and enhance git integration settings
2026-04-29 update workspace settings to associate .kicad_sch files with default editor
2026-04-29 update STM32 schematic UUID to match project standards
2026-04-29 core Refactor code structure for improved readability and maintainability
2026-04-29 update sym-lib-table to include additional library entries for JLCPCB components
2026-04-29 Update KiCad project and schematic files for z9-console - Changed project UUID in z9-console.kicad_pro to a new unique identifier. - Updated schematic version from 20250114 to 20260306 and generator 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
2026-04-29 Add dnt.kicad.libs/ to .gitignore for nested KiCad library repository
